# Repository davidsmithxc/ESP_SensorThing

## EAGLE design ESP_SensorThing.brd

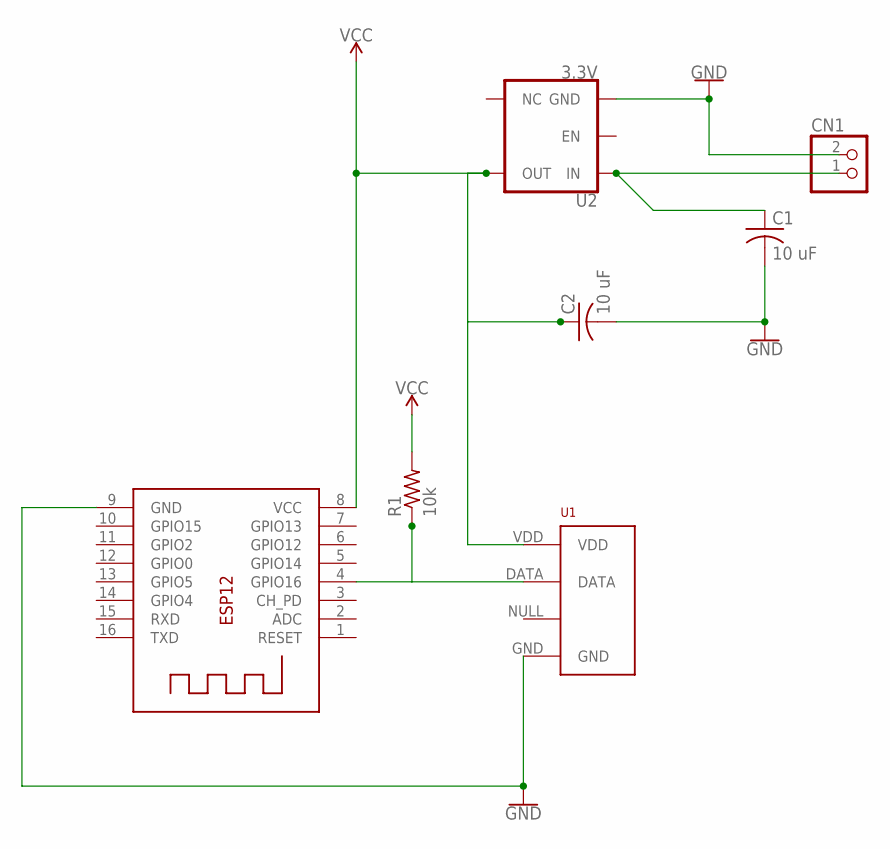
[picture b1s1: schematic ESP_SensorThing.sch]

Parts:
C1, C2: 10 uF; C1210
CN1: JST_2PIN-SMT-RA; JST-PH-2-SMT-RA
R1: 10k; R0805
U1: RHT03_DHT-22_AM2302RA; RHT03_DHT-22/RA
U2: 3.3V; SOT23-5
X1: ESP-12

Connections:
BATT: C1.1, CN1.1 (2), U2.1 (IN)
DATA: R1.1, U1.DATA, X1.4 (GPIO16)
GND: C1.2, C2.2, CN1.2 (1), U1.GND, U2.2 (GND), X1.9 (GND)
VCC: C2.1, R1.2, U1.VDD, U2.5 (OUT), X1.8 (VCC)

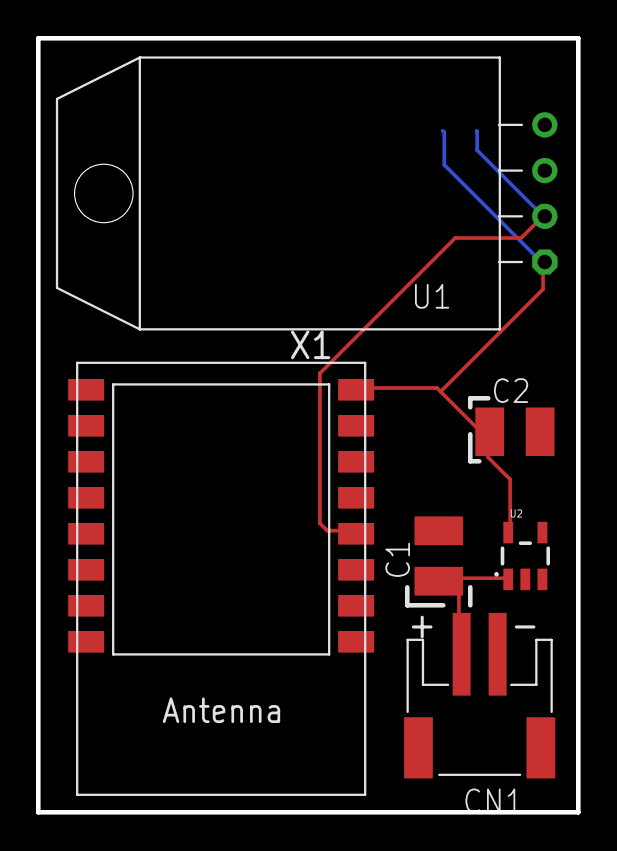
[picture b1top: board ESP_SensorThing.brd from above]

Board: 2 copper layers, 30.0 x 43.0 mm, 7 parts (1 on the bottom side), 4 nets.

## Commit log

2017-03-01 :boom::camel: Added .gitattributes & .gitignore files
2017-03-01 Initial creation

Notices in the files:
parts and their libraries:
SparkFun-IC-Power: Licensing: Creative Commons ShareAlike 4.0 International - https://creativecommons.org/licenses/by-sa/4.0
